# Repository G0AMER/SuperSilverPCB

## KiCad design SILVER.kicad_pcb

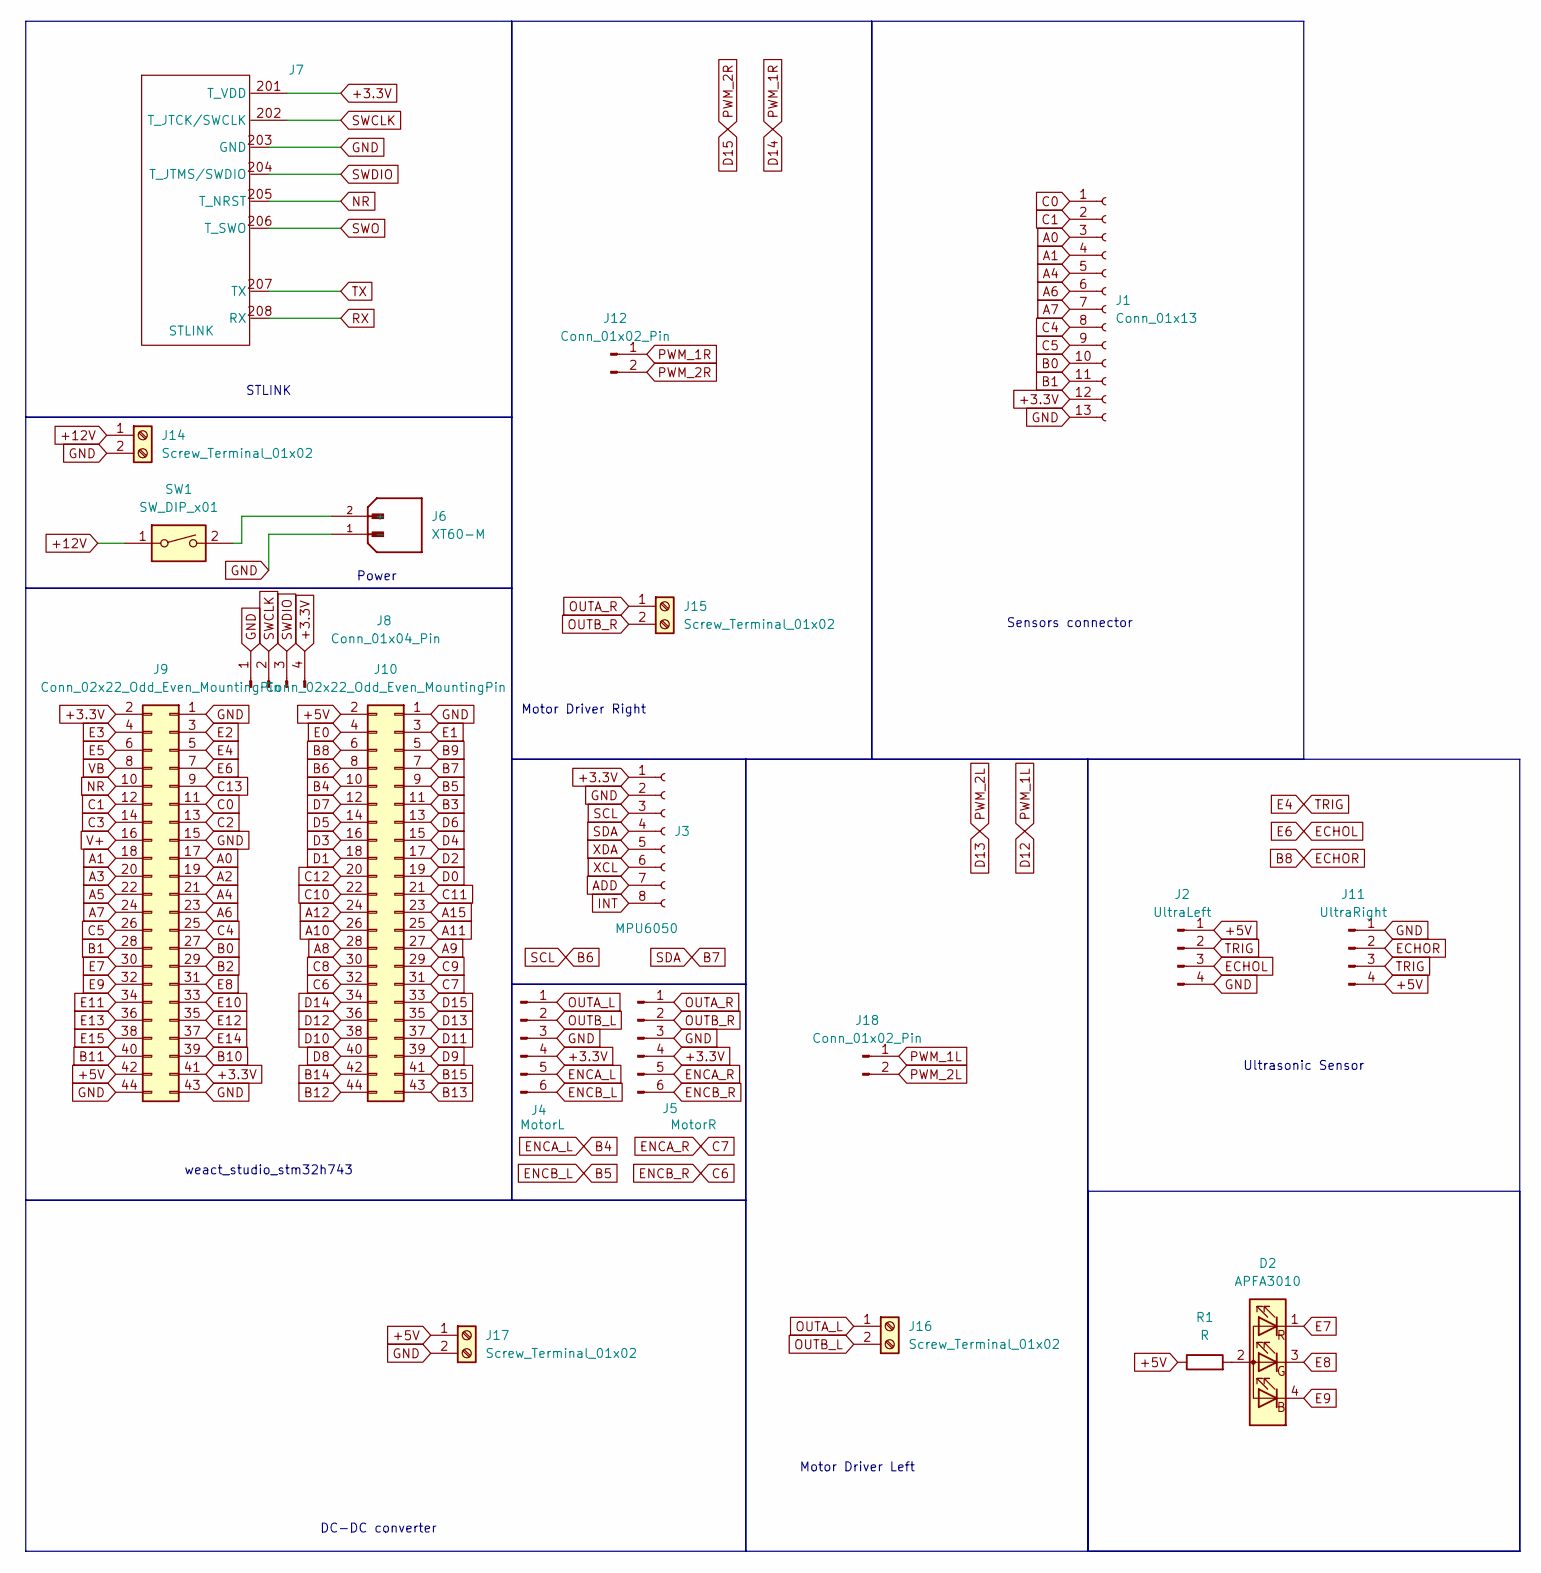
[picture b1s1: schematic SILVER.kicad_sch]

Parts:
D2: APFA3010; PinSocket_2x02_P2.54mm_Vertical
J1: Conn_01x13; PinHeader_1x13_P2.54mm_Vertical_SMD_Pin1Left
J2: UltraLeft; PinSocket_1x04_P2.54mm_Vertical
J3: MPU6050; PinSocket_1x08_P2.54mm_Vertical
J4: MotorL; PinHeader_1x06_P2.54mm_Vertical
J5: MotorR; PinHeader_1x06_P2.54mm_Vertical
J6: XT60-M; AMASS_XT60-M_1x02_P7.20mm_Vertical; PARTREV V1.2
J7: STLINK
J8: Conn_01x04_Pin; PinSocket_1x04_P2.54mm_Vertical
J9, J10: Conn_02x22_Odd_Even_MountingPin; PinSocket_2x22_P2.54mm_Vertical
J11: UltraRight; PinSocket_1x04_P2.54mm_Vertical
J12, J18: Conn_01x02_Pin; PinHeader_1x02_P2.54mm_Vertical
J14, J15, J16, J17: Screw_Terminal_01x02; TerminalBlock_MaiXu_MX126-5.0-02P_1x02_P5.00mm
R1: R; R_Axial_DIN0204_L3.6mm_D1.6mm_P2.54mm_Vertical
SW1: SW_DIP_x01; KCD11-101

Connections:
+3.3V: J1.12, J3.1, J4.4, J5.4, J7.201 (T_VDD), J8.4, J9.2, J9.41
+5V: J2.1, J9.42, J10.2, J11.4, J17.1, R1.1
+12V: J14.1, SW1.1
A0: J1.3, J9.17
A1: J1.4, J9.18
A2: J9.19
A3: J9.20
A4: J1.5, J9.21
A5: J9.22
A6: J1.6, J9.23
A7: J1.7, J9.24
A8: J10.28
A9: J10.27
A10: J10.26
A11: J10.25
A12: J10.24
A15: J10.23
ADD: J3.7
B0: J1.10, J9.27
B1: J1.11, J9.28
B2: J9.29
B3: J10.11
B4: J4.5, J10.10
B5: J4.6, J10.9
B6: J3.3, J10.8
B7: J3.4, J10.7
B8: J10.6, J11.2
B9: J10.5
B10: J9.39
B11: J9.40
B12: J10.44
B13: J10.43
B14: J10.42
B15: J10.41
C0: J1.1, J9.11
C1: J1.2, J9.12
C2: J9.13
C3: J9.14
C4: J1.8, J9.25
C5: J1.9, J9.26
C6: J5.6, J10.32
C7: J5.5, J10.31
C8: J10.30
C9: J10.29
C10: J10.22
C11: J10.21
C12: J10.20
C13: J9.9
D0: J10.19
D1: J10.18
D2: J10.17
D3: J10.16
D4: J10.15
D5: J10.14
D6: J10.13
D7: J10.12
D8: J10.40
D9: J10.39
D10: J10.38
D11: J10.37
D12: J10.36, J18.1
D13: J10.35, J18.2
D14: J10.34, J12.1
D15: J10.33, J12.2
E0: J10.4
E1: J10.3
E2: J9.3
E3: J9.4
E4: J2.2, J9.5, J11.3
E5: J9.6
E6: J2.3, J9.7
E7: D2.1 (R), J9.30
E8: D2.3 (G), J9.31
E9: D2.4 (B), J9.32
E10: J9.33
E11: J9.34
E12: J9.35
E13: J9.36
E14: J9.37
E15: J9.38
GND: J1.13, J2.4, J3.2, J4.3, J5.3, J6.1 (-), J7.203 (GND), J8.1, J9.1, J9.15, J9.43, J9.44, J10.1, J11.1, J14.2, J17.2
INT: J3.8
NR: J7.205 (T_NRST), J9.10
unnamed: D2.2 (A), R1.2
unnamed: J6.2 (+), SW1.2
OUTA_L: J4.1, J16.1
OUTA_R: J5.1, J15.1
OUTB_L: J4.2, J16.2
OUTB_R: J5.2 (M-), J15.2
RX: J7.208 (RX)
SWCLK: J7.202 (T_JTCK/SWCLK), J8.2
SWDIO: J7.204 (T_JTMS/SWDIO), J8.3
SWO: J7.206 (T_SWO)
TX: J7.207 (TX)
V+: J9.16
VB: J9.8
XCL: J3.6
XDA: J3.5

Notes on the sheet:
STLINK
Sensors connector
DC-DC converter
Motor Driver Right
Motor Driver Left
weact_studio_stm32h743
Power
Ultrasonic Sensor

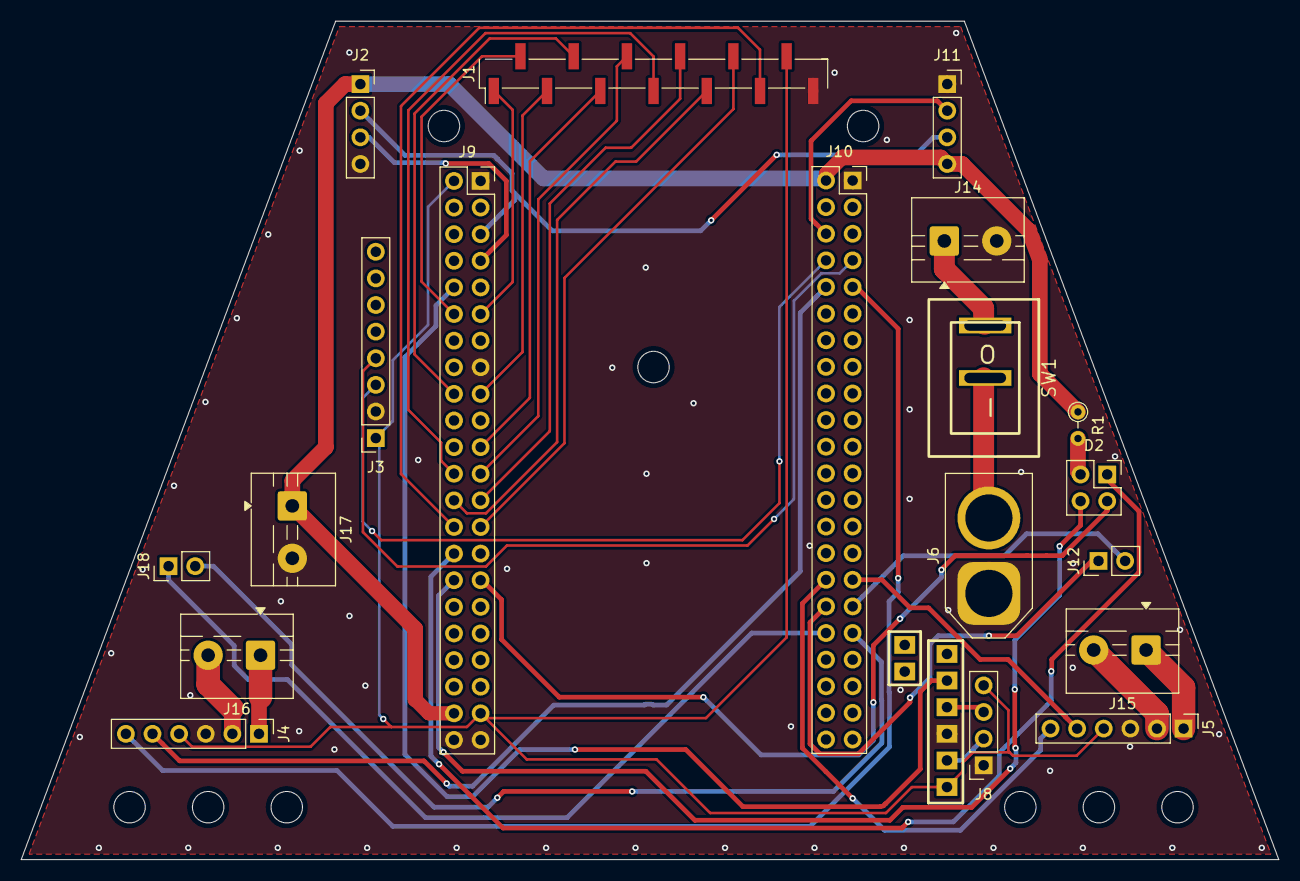
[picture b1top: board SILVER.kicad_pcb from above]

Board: 2 copper layers, 120.0 x 80.0 mm, 20 parts (0 on the bottom side), 40 nets.

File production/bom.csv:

Designator,Footprint,Quantity,Value,LCSC Part #
D2,PinSocket_2x02_P2.54mm_Vertical,1,APFA3010,
J1,PinHeader_1x13_P2.54mm_Vertical_SMD_Pin1Left,1,Conn_01x13,
"J10, J9",PinSocket_2x22_P2.54mm_Vertical,2,Conn_02x22_Odd_Even_MountingPin,
J11,PinSocket_1x04_P2.54mm_Vertical,1,UltraRight,
"J12, J18",PinHeader_1x02_P2.54mm_Vertical,2,Conn_01x02_Pin,
"J14, J15, J16, J17",TerminalBlock_MaiXu_MX126-5.0-02P_1x02_P5.00mm,4,Screw_Terminal_01x02,
J2,PinSocket_1x04_P2.54mm_Vertical,1,UltraLeft,
J3,PinSocket_1x08_P2.54mm_Vertical,1,MPU6050,
J4,PinHeader_1x06_P2.54mm_Vertical,1,MotorL,
J5,PinHeader_1x06_P2.54mm_Vertical,1,MotorR,
J6,AMASS_XT60-M_1x02_P7.20mm_Vertical,1,XT60-M,
J8,PinSocket_1x04_P2.54mm_Vertical,1,Conn_01x04_Pin,
R1,R_Axial_DIN0204_L3.6mm_D1.6mm_P2.54mm_Vertical,1,R,
SW1,KCD11-101,1,SW_DIP_x01,

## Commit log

2025-12-01 feat: Add new dc-dc converter and VNH5019 motor driver projects, update main schematic with motor connectors.
2025-12-06 feat: Introduce LM2596 and STLINK KiCad projects with new symbols and footprints, and update the main SILVER project.
2025-12-07 feat: Update main project schematic and PCB with new component footprint and connector details, and add new RB141C1100 component files.
2025-12-15 Added ultrasonic sensor placement
2025-12-18 added pcb outline
2026-01-15 pcbv1.0
2026-01-20 SILVER PCB v2.0
2026-01-22 Cleaned up the middle traces and right edge 5v trace
2026-01-23 PCB v3.0
2026-01-28 final
2026-01-30 feat: Update KiCad PCB design, regenerate manufacturing Gerber files, and refresh production outputs.
